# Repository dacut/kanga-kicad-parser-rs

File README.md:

# kanga-kicad-parser-rs
Rust parser for KiCAD files

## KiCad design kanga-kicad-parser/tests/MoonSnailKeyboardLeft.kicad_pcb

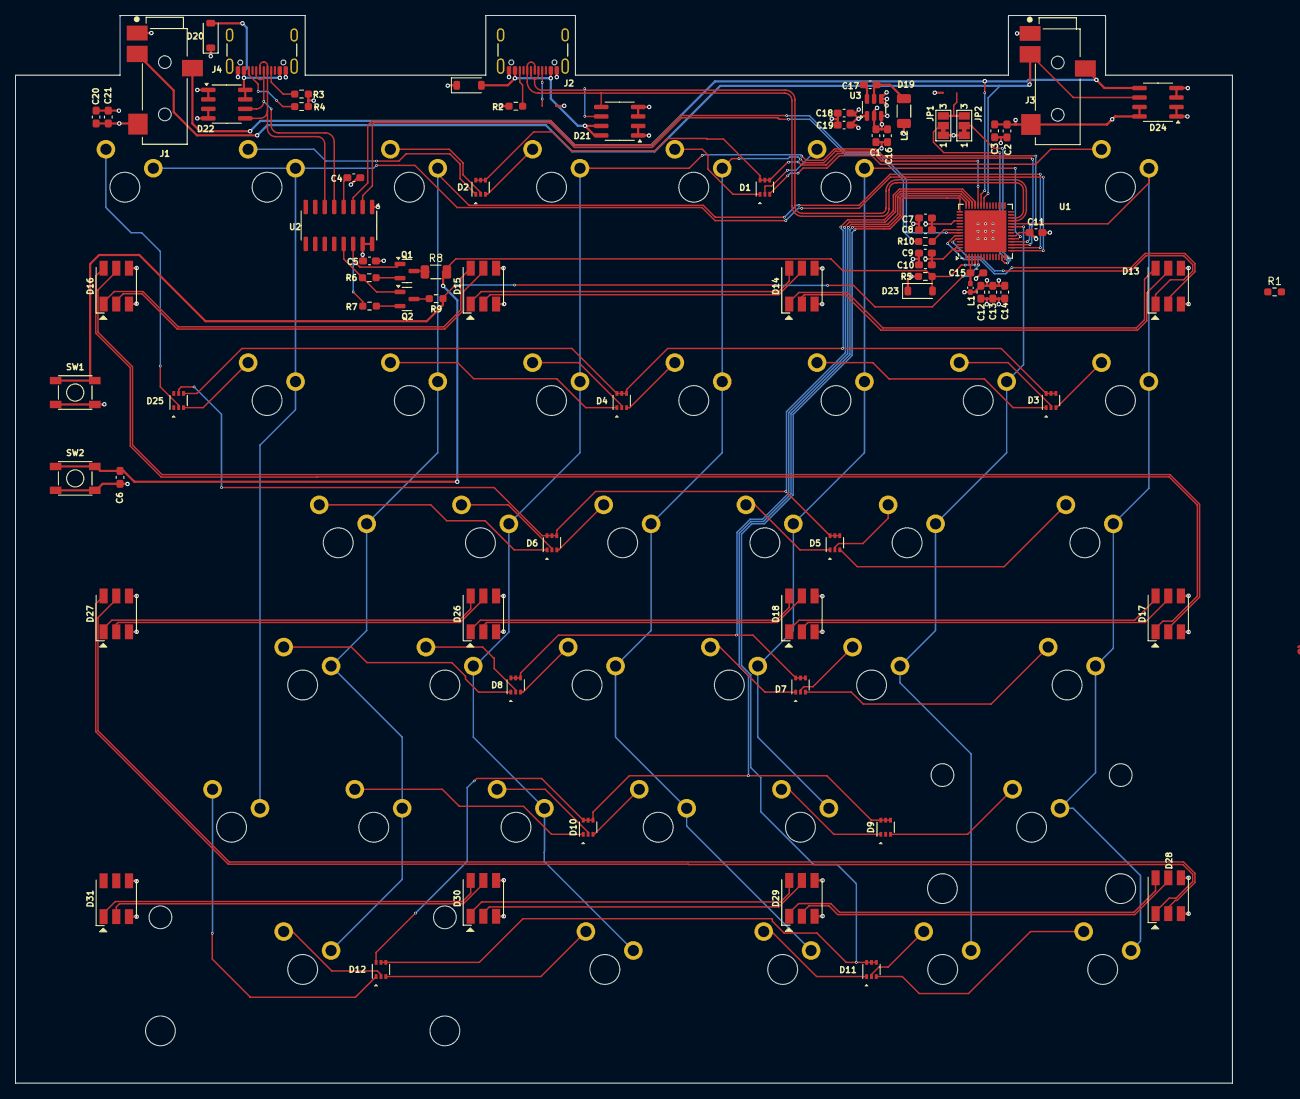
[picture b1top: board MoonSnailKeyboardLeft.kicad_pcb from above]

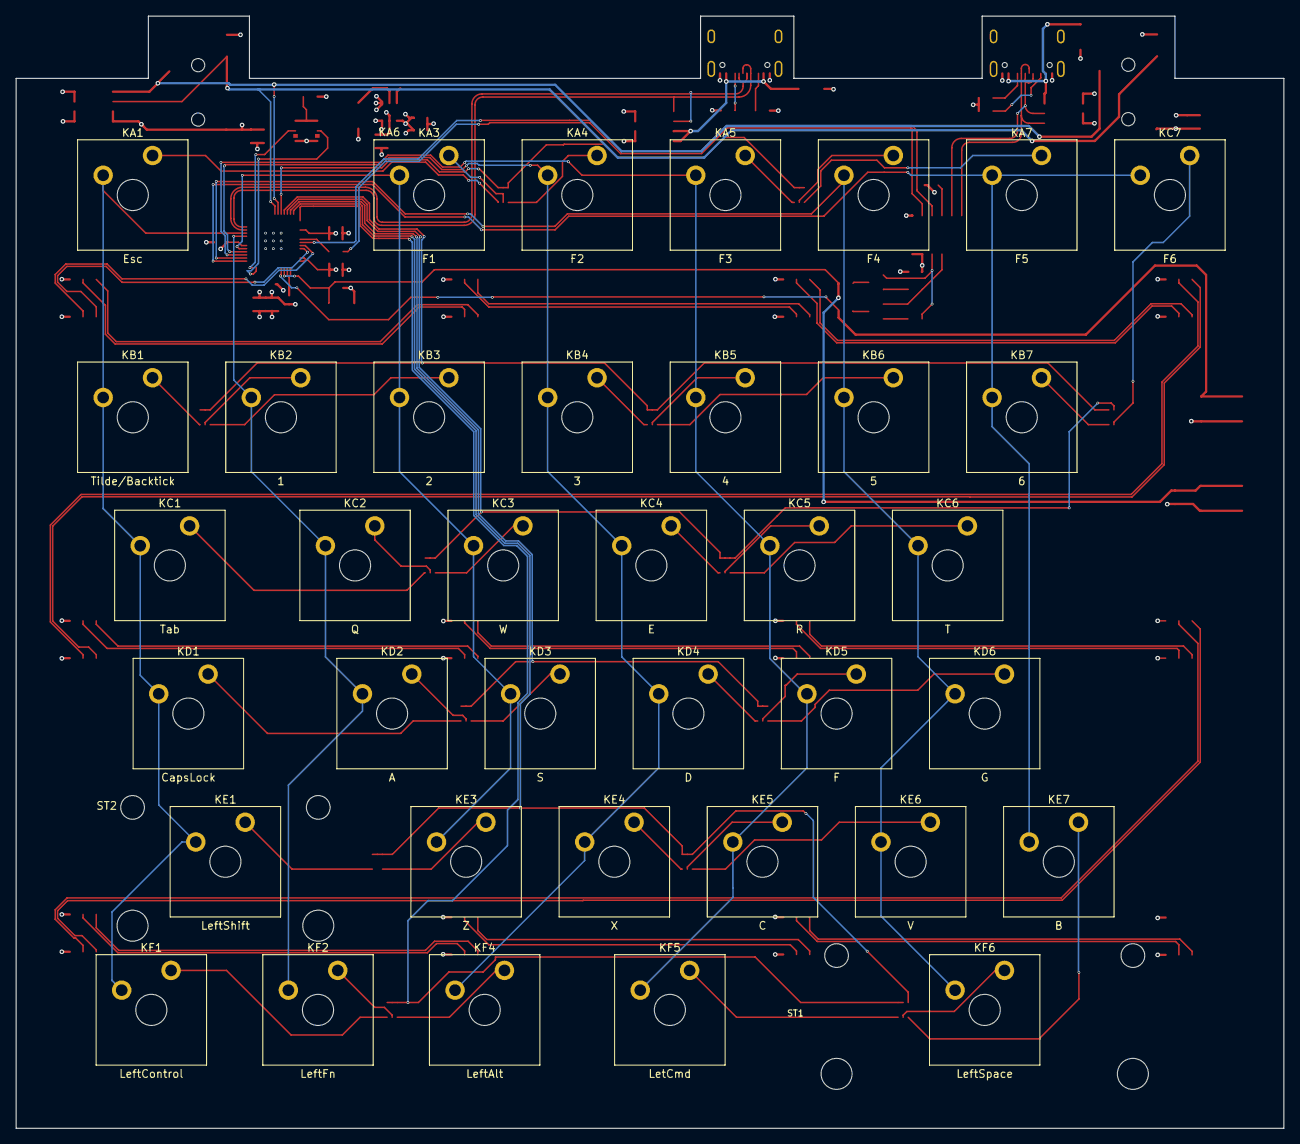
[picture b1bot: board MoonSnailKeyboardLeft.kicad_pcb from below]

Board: 4 copper layers, 163.0 x 143.0 mm, 116 parts (39 on the bottom side), 107 nets.

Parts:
C1, C2, C5, C12, C16, C20: 10 uF; C_0603_1608Metric_Pad1.08x0.95mm_HandSolder
C3, C10, C21: 10 nF; C_0603_1608Metric_Pad1.08x0.95mm_HandSolder
C4, C6, C8, C11, C14, C15, C17: 100 nF; C_0603_1608Metric_Pad1.08x0.95mm_HandSolder
C7, C9, C13: 1 uF; C_0603_1608Metric_Pad1.08x0.95mm_HandSolder
C18, C19: 22 uF; C_0603_1608Metric_Pad1.08x0.95mm_HandSolder
D1, D2, D3, D4, D5, D6, D7, D8, D9, D10, D11, D12, D25: MMBD4148TW-7-F; SOT-363_SC-70-6
D13, D14, D15, D16, D17, D18, D26, D27, D28, D29, D30, D31: BL-HBGR32L-3-TRB-8; LED_RGB_5050-6
D19, D20, D23: 1N5819HW-7-F; D_SOD-123
D21, D22, D24: SMDA05CDR2G; SOIC-8_3.9x4.9mm_P1.27mm
J1, J3: SJ-43514-SMT; CUI_SJ-43514-SMT
J2, J4: USB_C_Receptacle_USB2.0_14P; USB_C_Receptacle_GCT_USB4105-xx-A_16P_TopMnt_Horizontal
JP1, JP2: Solder Jumper; Jumper3-12
KA1, KA3, KA4, KA5, KA6, KA7: SW_Push; SW_Cherry_MX_Plate_1.00u
KB1, KB2, KB3, KB4, KB5, KB6, KB7: SW_Push; SW_Cherry_MX_Plate_1.00u
KC1: SW_Push; SW_Cherry_MX_Plate_1.50u
KC2, KC3, KC4, KC5, KC6, KC7: SW_Push; SW_Cherry_MX_Plate_1.00u
KD1: SW_Push; SW_Cherry_MX_Plate_1.75u
KD2, KD3, KD4, KD5, KD6: SW_Push; SW_Cherry_MX_Plate_1.00u
KE1: SW_Push; SW_Cherry_MX_Plate_2.25u
KE3, KE4, KE5, KE6, KE7: SW_Push; SW_Cherry_MX_Plate_1.00u
KF1, KF4, KF5: SW_Push; SW_Cherry_MX_Plate_1.25u
KF2: SW_Push; SW_Cherry_MX_Plate_1.00u
KF6: SW_Push; SW_Cherry_MX_Plate_3.00u
L1: 2 nH; L_0402_1005Metric_Pad0.77x0.64mm_HandSolder
L2: 3.9 uH; L_1206_3216Metric_Pad1.22x1.90mm_HandSolder
Q1, Q2: SS8050-G; SOT-23
R1, R2, R3, R4: 5.1 k; R_0603_1608Metric_Pad0.98x0.95mm_HandSolder
R5, R6, R7: 10 k; R_0603_1608Metric_Pad0.98x0.95mm_HandSolder
R8: 0; C_1206_3216Metric
R9: 0; R_0603_1608Metric_Pad0.98x0.95mm_HandSolder
R10: 499; R_0603_1608Metric_Pad0.98x0.95mm_HandSolder
ST1: Stabilizer; Stabilizer_Cherry_MX_3.00u
ST2: Stabilizer; Stabilizer_Cherry_MX_2.00u
SW1, SW2: PTS 647 SM38 SMTR2 LFS; CK-PTS647
U1: ESP32-S3-PICO-1; QFN-56-1EP_7x7mm_P0.4mm_EP5.6x5.6mm
U2: CH340C; SOIC-16_3.9x9.9mm_P1.27mm
U3: AP63203WU; TSOT-23-6

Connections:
+3V3: C7.1, C8.1, C9.1, C10.1, C11.1, C12.1, C13.1, C14.1, C18.1, C19.1, D23.1 (K), L1.1, L2.2, R5.1, U1.20 (VDD3P3_RTC), U1.46 (VDD3P3_CPU), U1.55 (VDDA), U1.56 (VDDA), U3.1 (FB)
+5V: C1.1, C2.1, C3.1, C5.1, C16.1, C20.1, C21.1, D13.4 (VCC), D14.4 (VCC), D15.4 (VCC), D16.4 (VCC), D17.4 (VCC), D18.4 (VCC), D19.1 (K), D20.1 (K), D24.7, D24.8, D26.4 (VCC), D27.4 (VCC), D28.4 (VCC), D29.4 (VCC), D30.4 (VCC), D31.4 (VCC), J1.2, J3.2, U2.15 (R232), U2.16 (VCC), U3.2 (EN), U3.3 (IN)
/Keyboard/COL1: KA1.1, KB1.1, KC1.1, KD1.1, KE1.1, KF1.1, U1.24 (GPIO18/ADC2_CH7)
/Keyboard/COL2: KB2.1, KC2.1, KD2.1, KF2.1, U1.23 (GPIO17/ADC2_CH6)
/Keyboard/COL3: KA3.1, KB3.1, KC3.1, KD3.1, KE3.1, U1.19 (GPIO14/ADC2_CH3)
/Keyboard/COL4: KA4.1, KB4.1, KC4.1, KD4.1, KE4.1, KF4.1, U1.18 (GPIO13/ADC2_CH2)
/Keyboard/COL5: KA5.1, KB5.1, KC5.1, KD5.1, KE5.1, KF5.1, U1.17 (GPIO12/ADC2_CH1)
/Keyboard/COL6: KA6.1, KB6.1, KC6.1, KD6.1, KE6.1, KF6.1, U1.16 (GPIO11/ADC2_CH0)
/Keyboard/COL7: KA7.1, KB7.1, KC7.1, KE7.1, U1.15 (GPIO10/ADC1_CH9)
/Keyboard/RGBCLK: D13.2 (CI), U1.51 (GPIO45)
/Keyboard/RGBDI: D13.1 (DI), U1.52 (GPIO46)
/Keyboard/ROWA: D1.4 (K), D1.5 (K), D1.6 (K), D2.4 (K), D2.5 (K), D2.6 (K), U1.38 (GPIO33)
/Keyboard/ROWB: D3.4 (K), D3.5 (K), D3.6 (K), D4.4 (K), D4.5 (K), D4.6 (K), D25.4 (K), U1.39 (GPIO34)
/Keyboard/ROWC: D5.4 (K), D5.5 (K), D5.6 (K), D6.4 (K), D6.5 (K), D6.6 (K), D25.5 (K), U1.40 (GPIO35)
/Keyboard/ROWD: D7.4 (K), D7.5 (K), D7.6 (K), D8.4 (K), D8.5 (K), D8.6 (K), U1.41 (GPIO36)
/Keyboard/ROWE: D9.4 (K), D9.5 (K), D9.6 (K), D10.4 (K), D10.5 (K), D10.6 (K), D12.6 (K), U1.42 (GPIO37)
/Keyboard/ROWF: D11.4 (K), D11.5 (K), D11.6 (K), D12.4 (K), D12.5 (K), U1.43 (GPIO38)
/MCU/BOOT: R9.2, SW1.1, SW1.2, U1.5 (GPIO0/BOOT)
/MCU/DTR: Q2.1 (E), R6.2, U2.13 (~DTR)
/MCU/KBD_TYPE_0: JP1.2 (C), U1.13 (GPIO8/ADC1_CH7)
/MCU/KBD_TYPE_1: JP2.2 (C), U1.14 (GPIO9/ADC1_CH8)
/MCU/RESET: C6.1, D23.2 (A), R5.2, R8.2, SW2.1, SW2.2, U1.4 (CHIP_PU/RESET)
/MCU/RTS: Q1.1 (E), R7.1, U2.14 (~RTS)
/MCU/RXD: U1.50 (U0RXD/PROG/GPIO44), U2.3 (RXD)
/MCU/SCL: D24.6, J1.4, J3.4, U1.36 (SPICLK_N/GPIO48)
/MCU/SDA: D24.5, J1.3, J3.3, U1.37 (SPICLK_P/GPIO47)
/MCU/TXD: R10.2, U2.2 (TXD)
/MCU/USB_D+: D21.5, J2.A6 (D+), J2.B6 (D+), U1.26 (GPIO20/USB_D+/ADC2_CH9)
/MCU/USB_D-: D21.6, J2.A7 (D-), J2.B7 (D-), U1.25 (GPIO19/USB_D-/ADC2_CH8)
/Ports/VBUS_USB: D19.2 (A), D21.7, D21.8, J2.A4 (VBUS), J2.A9 (VBUS), J2.B4 (VBUS), J2.B9 (VBUS)
/Ports/VBUS_USB_PGM: D20.2 (A), D22.7, D22.8, J4.A4 (VBUS), J4.A9 (VBUS), J4.B4 (VBUS), J4.B9 (VBUS)
GND: C1.2, C2.2, C3.2, C4.2, C5.2, C6.2, C7.2, C8.2, C9.2, C10.2, C11.2, C12.2, C13.2, C14.2, C15.2, C16.2, C18.2, C19.2, C20.2, C21.2, D13.3 (GND), D14.3 (GND), D15.3 (GND), D16.3 (GND), D17.3 (GND), D18.3 (GND), D21.1, D21.2, D21.3, D21.4, D22.1, D22.2, D22.3, D22.4, D24.1, D24.2, D24.3, D24.4, D26.3 (GND), D27.3 (GND), D28.3 (GND), D29.3 (GND), D30.3 (GND), D31.3 (GND), J1.1, J2.A1 (GND), J2.A12 (GND), J2.B1 (GND), J2.B12 (GND), J2.S1 (SHIELD), J3.1, J4.A1 (GND), J4.A12 (GND), J4.B1 (GND), J4.B12 (GND), J4.S1 (SHIELD), JP1.1 (A), JP2.1 (A), R1.2, R2.2, R3.2, R4.2, SW1.3, SW1.4, SW2.3, SW2.4, U1.57 (GND), U2.1 (GND), U3.4 (GND)
unnamed: D1.1 (A), KA4.2
unnamed: D1.2 (A), KA3.2
unnamed: D1.3 (A), KA1.2
unnamed: D2.1 (A), KA7.2
unnamed: D2.2 (A), KA6.2
unnamed: D2.3 (A), KA5.2
unnamed: D3.1 (A), KB3.2
unnamed: D3.2 (A), KB2.2
unnamed: D3.3 (A), KB1.2
unnamed: D4.1 (A), KB6.2
unnamed: D4.2 (A), KB5.2
unnamed: D4.3 (A), KB4.2
unnamed: D5.1 (A), KC3.2
unnamed: D5.2 (A), KC2.2
unnamed: D5.3 (A), KC1.2
unnamed: D6.1 (A), KC6.2
unnamed: D6.2 (A), KC5.2
unnamed: D6.3 (A), KC4.2
unnamed: D7.1 (A), KD3.2
unnamed: D7.2 (A), KD2.2
unnamed: D7.3 (A), KD1.2
unnamed: D8.1 (A), KD6.2
unnamed: D8.2 (A), KD5.2
unnamed: D8.3 (A), KD4.2
unnamed: D9.1 (A), KE3.2
unnamed: D9.3 (A), KE1.2
unnamed: D10.1 (A), KE6.2
unnamed: D10.2 (A), KE5.2
unnamed: D10.3 (A), KE4.2
unnamed: D11.1 (A), KF4.2
unnamed: D11.2 (A), KF2.2
unnamed: D11.3 (A), KF1.2
unnamed: D12.1 (A), KE7.2
unnamed: D12.2 (A), KF6.2
unnamed: D12.3 (A), KF5.2
unnamed: D13.5 (CO), D14.2 (CI)
unnamed: D13.6 (DO), D14.1 (DI)
unnamed: D14.5 (CO), D15.2 (CI)
unnamed: D14.6 (DO), D15.1 (DI)
unnamed: D15.5 (CO), D16.2 (CI)
unnamed: D15.6 (DO), D16.1 (DI)
unnamed: D16.5 (CO), D17.2 (CI)
unnamed: D16.6 (DO), D17.1 (DI)
unnamed: D17.5 (CO), D18.2 (CI)
unnamed: D17.6 (DO), D18.1 (DI)
unnamed: D18.5 (CO), D26.2 (CI)
unnamed: D18.6 (DO), D26.1 (DI)
unnamed: D25.2 (A), KC7.2
unnamed: D25.3 (A), KB7.2
unnamed: D26.5 (CO), D27.2 (CI)
unnamed: D26.6 (DO), D27.1 (DI)
unnamed: D27.5 (CO), D28.2 (CI)
unnamed: D27.6 (DO), D28.1 (DI)
unnamed: D28.5 (CO), D29.2 (CI)
unnamed: D28.6 (DO), D29.1 (DI)
unnamed: D29.5 (CO), D30.2 (CI)
unnamed: D29.6 (DO), D30.1 (DI)
unnamed: D30.5 (CO), D31.2 (CI)
unnamed: D30.6 (DO), D31.1 (DI)
unnamed: J2.A5 (CC1), R1.1
unnamed: J2.B5 (CC2), R2.1
unnamed: J4.A5 (CC1), R3.1
unnamed: J4.B5 (CC2), R4.1
unnamed: JP1.3 (B), JP2.3 (B)
unnamed: Q1.2 (B), R6.1
unnamed: Q1.3 (C), R8.1
unnamed: Q2.2 (B), R7.2
unnamed: Q2.3 (C), R9.1
unnamed: R10.1, U1.49 (U0TXD/PROG/GPIO43)
unnamed: D22.6, J4.A6 (D+), J4.B6 (D+), U2.5 (UD+)
unnamed: D22.5, J4.A7 (D-), J4.B7 (D-), U2.6 (UD-)
unnamed: C4.1, U2.4 (V3)
unnamed: C17.2, U3.6 (BST)
unnamed: C17.1, L2.1, U3.5 (SW)
VDD3P3: C15.1, L1.2, U1.2 (VDD3P3), U1.3 (VDD3P3)

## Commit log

2025-03-22 Failed attempt 1
2025-03-24 Working declarations
2025-03-26 Not debugged, but first complete impl
